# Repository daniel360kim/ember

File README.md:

# Ember

**A differentiable 6-DOF rocket simulator that trains a neural flight controller by backpropagating through physics.**

Ember is an end-to-end platform for developing thrust-vector-controlled (TVC) model rockets: a fully differentiable PyTorch flight dynamics engine, a neural attitude-control policy trained directly through the simulated physics, and a custom flight computer to fly the learned controller on real hardware.

The core idea is **differentiable simulation** (a.k.a. "diffsim"). Instead of treating the physics engine as an opaque, non-differentiable black box and learning a controller with reinforcement learning, Ember implements the entire 6-DOF rigid-body simulation in PyTorch so that gradients flow *through* every integration step, every aerodynamic force, and every actuator model. The attitude error at the end of a flight can be differentiated all the way back to the neural network's weights, letting the controller be optimized with plain gradient descent — the same way you would train any other neural network.

---

## Project status

Ember is an active work in progress. The current state:

**Working today**

- Complete, batched, GPU-ready 6-DOF differentiable physics (motor, TVC gimbal, aerodynamics, time-varying mass), integrated with RK4 and quaternion attitude kinematics.
- Batched rollout stack (`RocketEnv` + `EpisodeManager`) with flight-phase termination (burnout, ground impact, excessive tilt).
- A neural MLP attitude controller trained end-to-end through the physics via autograd, plus a PID baseline.
- Declarative YAML vehicle configuration.
- An extensive test suite (~40+ tests) including explicit gradient-flow verification.
- A custom Teensy-based flight computer designed in KiCad (`hardware/`).

**On the roadmap**

- Fully config-driven training/eval runners (task and hyperparameter YAML layers).
- Domain randomization over motor thrust, mass, servo lag, and drag for robust sim-to-real transfer.
- Trajectory-length masking of the loss past episode termination.
- Experiment logging, checkpointing, and a dedicated evaluation runner.
- Export of the trained policy to run in real time on the flight computer, closing the sim-to-hardware loop.

---

## Why differentiable simulation?

Learning a controller for an unstable, fast, safety-critical system like a TVC rocket is hard. The two conventional options each have a major drawback:

- **Reinforcement learning (RL)** treats the simulator as a black box and estimates gradients from scalar rewards. This works, but it is notoriously *sample-inefficient* — it throws away all the structure of the physics and needs enormous numbers of rollouts to converge.
- **Classical control (PID, LQR)** is sample-free but requires hand-tuning and a linearized model, and it struggles with the strongly time-varying, nonlinear dynamics of a rocket whose mass, center of gravity, and inertia change every millisecond as propellant burns.

Differentiable simulation gets the best of both. Because the physics engine is written in an autodiff framework, the *analytic gradient* of the flight outcome with respect to the controller parameters is available for free. Training becomes a direct optimization problem:

> "Given this rocket, what network weights minimize the attitude error over the boost phase?"

This is dramatically more sample-efficient than RL and far more flexible than classical control, because the exact gradient — not a noisy estimate — points the optimizer in the right direction on every single rollout.

```
                            ┌─────────────────────────────────────────────┐
   setpoint (upright) ─────►│  Neural Policy (MLP)                         │
                            │  attitude error + body rates → gimbal command│
                            └───────────────────┬─────────────────────────┘
                                                │  U (2-axis TVC torque cmd)
                                                ▼
        ┌───────────────────────────────────────────────────────────────┐
        │  Differentiable 6-DOF Physics (PyTorch)                        │
        │  motor thrust · TVC gimbal · aerodynamics · time-varying mass  │
        │  RK4 integration · quaternion attitude kinematics              │
        └───────────────────────────┬───────────────────────────────────┘
                                     │  trajectory X(t)   (fully differentiable)
                                     ▼
                            ┌────────────────────┐
                            │  Attitude-error    │
                            │  loss              │
                            └─────────┬──────────┘
                                      │
     ◄────────────────────────────────┘
        loss.backward(): gradient flows through the ENTIRE rollout,
        through every RK4 step and physics term, back to the MLP weights.
```

---

## How the differentiable simulation works

Everything in the physics path is a `torch.Tensor` operation, so the whole rollout is a single differentiable computation graph. A few deliberate engineering choices keep that graph intact and its gradients well-behaved:

- **Autograd through the integrator.** The RK4 step chains four evaluations of the vehicle dynamics per timestep, and every one is differentiable — the full trajectory is one continuous graph from initial condition to final state.

```21:27:simulation/src/vehicle/integrators.py
def rk4_step(...):
    k1 = dynamics_fn(X, U, t)
    k2 = dynamics_fn(X + dt / 2 * k1, U, t + dt / 2)
    k3 = dynamics_fn(X + dt / 2 * k2, U, t + dt / 2)
    k4 = dynamics_fn(X + dt * k3, U, t + dt)
    X_new = X + (dt / 6) * (k1 + 2 * k2 + 2 * k3 + k4)
```

- **Out-of-place quaternion normalization.** After each step the attitude quaternion is renormalized by constructing a *new* tensor rather than mutating in place, so backpropagation through the projection is safe (in-place writes are a classic way to silently break an autograd graph).

- **Branch-free physics.** Discontinuous logic — like the piecewise F15 thrust curve — is written with `torch.where` instead of Python `if` statements, so gradients propagate across every phase of the burn.

- **Gradient-safe numerics.** Operations that can produce infinite gradients (e.g. `arccos` at `±1` when computing angle of attack) clamp their inputs away from the singularity, keeping training stable.

Because the physics is written this way, `loss.backward()` on the training loss populates gradients on the neural network's parameters through thousands of chained physics operations, and a standard `Adam` optimizer step improves the controller. There is no reward function, no value network, and no policy-gradient estimator — just supervised optimization of a trajectory-level loss.

```53:69:simulation/src/runners/train_runner.py
        for i in range(N_EPOCHS):
            initial_state = torch.zeros(BATCH_DIM, S.DIM)
            initial_state[..., S.ORI] = start_orientation

            history = episode_runner.run(
                initial_state=initial_state,
                setpoint=setpoint,
                policy=policy,
                vehicle=self.vehicle,
            )

            loss = self.calculate_loss(history.to_episode_result(), setpoint=setpoint)

            print(f"Epoch {i + 1}/{N_EPOCHS} — loss: {loss.item():.6f}")
            optimizer.zero_grad()
            loss.backward()
            optimizer.step()
```

---

## The physics model

Ember simulates a full six-degree-of-freedom rigid body with a compact, batched 15-dimensional state vector (`simulation/src/vehicle/state.py`):

| State           | Indices | Description                                          |
| --------------- | :-----: | ---------------------------------------------------- |
| Position        | `0:3`   | World-frame position (Z up)                          |
| Orientation     | `3:7`   | Attitude quaternion, scalar-last `[x, y, z, w]`      |
| Velocity        | `7:10`  | World-frame linear velocity                          |
| Angular velocity| `10:13` | Body-frame angular rates                             |
| Gimbal angle    | `13:15` | 2-axis TVC deflections `(δx, δy)`                    |

Each timestep, the vehicle sums the physical forces and torques and integrates the rigid-body equations of motion. The physics is decomposed into independently-testable, composable components:

- **Motor** — a piecewise-polynomial F15 thrust curve with analytic total impulse and a time-varying propellant mass / moment-of-inertia model (inside-out burn).
- **Cartesian TVC gimbal** — a 2-axis thrust-vectoring actuator that tilts the thrust vector, with a first-order servo lag between commanded and actual deflection.
- **Aerodynamics** — quadratic drag, Barrowman-style normal force, and a pitch-damping moment.
- **Mass properties** — combines the dry airframe and burning motor, shifting the center of gravity and inertia tensor (via the parallel-axis theorem) as propellant is consumed.
- **Rigid-body core** — Newton–Euler dynamics including the gyroscopic term `ω × (Iω)`, integrated with swappable explicit-Euler or RK4 schemes.

The entire vehicle is specified declaratively in YAML (`simulation/configs/vehicles/atlas.yaml`) — mass, motor, geometry, aero coefficients, and gimbal limits — so a rocket is fully described by data rather than code.

---

## The neural controller

The policy is a small multilayer perceptron (`simulation/src/policy/mlp.py`) — deliberately kept tiny so it can eventually be exported and run in real time on a microcontroller. It observes the *shortest-path* body-frame attitude error (the x/y components of the error quaternion) together with the body angular rates, and outputs a 2-axis gimbal torque command squashed through `tanh` to respect the actuator's physical limits.

```26:38:simulation/src/policy/mlp.py
    def forward(self, X, setpoint):
        q  = normalize_quat(X[..., S.ORI])
        w_b = X[..., S.ANG_VEL]
        setpoint = normalize_quat(setpoint.expand(*q.shape[:-1], 4))

        q_error = quat_mul(quat_inv(q), setpoint)
        q_error = q_error * torch.where(q_error[..., 3:4] < 0, -1., 1.)
        error   = q_error[..., :2]

        input = torch.cat([error, X[..., S.ANG_VEL]], dim=-1)
        output = self.network(input)
        return self.max_output * torch.tanh(output)
```

A conventional **PID controller** (`simulation/src/policy/pid.py`) is included as a baseline for comparison against the learned policy.

---

## Quick start

Requires Python 3.10+.

```bash
git clone https://github.com/daniel360kim/ember.git
cd ember/simulation
pip install -e .
```

This installs `torch`, `numpy`, `matplotlib`, and `pyyaml`, and puts `src/` on the import path so `from vehicle.atlas_v1 import Atlas`-style imports resolve.

### Train the neural controller through the physics

```bash
cd ember/simulation
PYTHONPATH=src python src/runners/train_runner.py
```

This builds the `Atlas` vehicle, rolls it out under the MLP policy from a slightly tilted initial attitude, computes the attitude-error loss over the boost, and backpropagates through the entire flight to update the network — for 100 epochs. It plots the orientation and gimbal histories at the first, middle, and last epoch so you can watch the controller learn to stabilize the rocket.

### Run the test suite

The physics engine is covered by an extensive suite of unit and integration tests, including explicit checks that gradients flow correctly through the integrators, the rigid-body core, and the full vehicle dynamics.

```bash
cd ember/simulation
pytest                 # everything
pytest tests/vehicle/  # physics component & dynamics tests
pytest tests/runners/  # environment & rollout integration tests
```

---

## Repository layout

```
ember/
├── simulation/                     # Differentiable PyTorch simulator (main project)
│   ├── src/
│   │   ├── vehicle/                # 6-DOF physics
│   │   │   ├── atlas_v1.py         # Concrete rocket: assembles the full dynamics
│   │   │   ├── base_vehicle.py     # Vehicle interface + quaternion projection
│   │   │   ├── rigid_body.py       # Newton–Euler derivative core
│   │   │   ├── mass_properties.py  # Time-varying mass / CG / inertia
│   │   │   ├── integrators.py      # euler_step, rk4_step (differentiable)
│   │   │   ├── state.py            # 15-D state-vector layout
│   │   │   └── components/         # motor, cartesian_gimbal (TVC), aero
│   │   ├── policy/
│   │   │   ├── mlp.py              # Neural attitude controller
│   │   │   └── pid.py              # Classical baseline
│   │   ├── runners/
│   │   │   ├── rocket_env.py       # Batched, Gym-like physics environment
│   │   │   ├── episode_manager.py  # Policy-in-the-loop rollout engine
│   │   │   └── train_runner.py     # Differentiable training entry point
│   │   └── utils/math.py           # Quaternion algebra & kinematics
│   ├── configs/vehicles/atlas.yaml # Declarative vehicle definition
│   └── tests/                      # Physics unit tests + gradient-flow checks
│
├── hardware/                       # Custom flight computer (KiCad)
│   └── pcb/flight_computer/        # Teensy-based board: IMU, barometer,
│                                   # servo drivers, pyro channels, power
└── background/                     # Early diffsim prototypes & experiments
```

---

## Hardware

The `hardware/` directory contains the KiCad design for a custom rocket flight computer — a Teensy-class board with an IMU, barometer, servo drivers for the TVC gimbal, pyro channels for recovery, and power management. The long-term goal of Ember is **zero-shot sim-to-real transfer**: train the attitude controller entirely in the differentiable simulator, then deploy the exact learned weights to this board to fly a physical rocket.

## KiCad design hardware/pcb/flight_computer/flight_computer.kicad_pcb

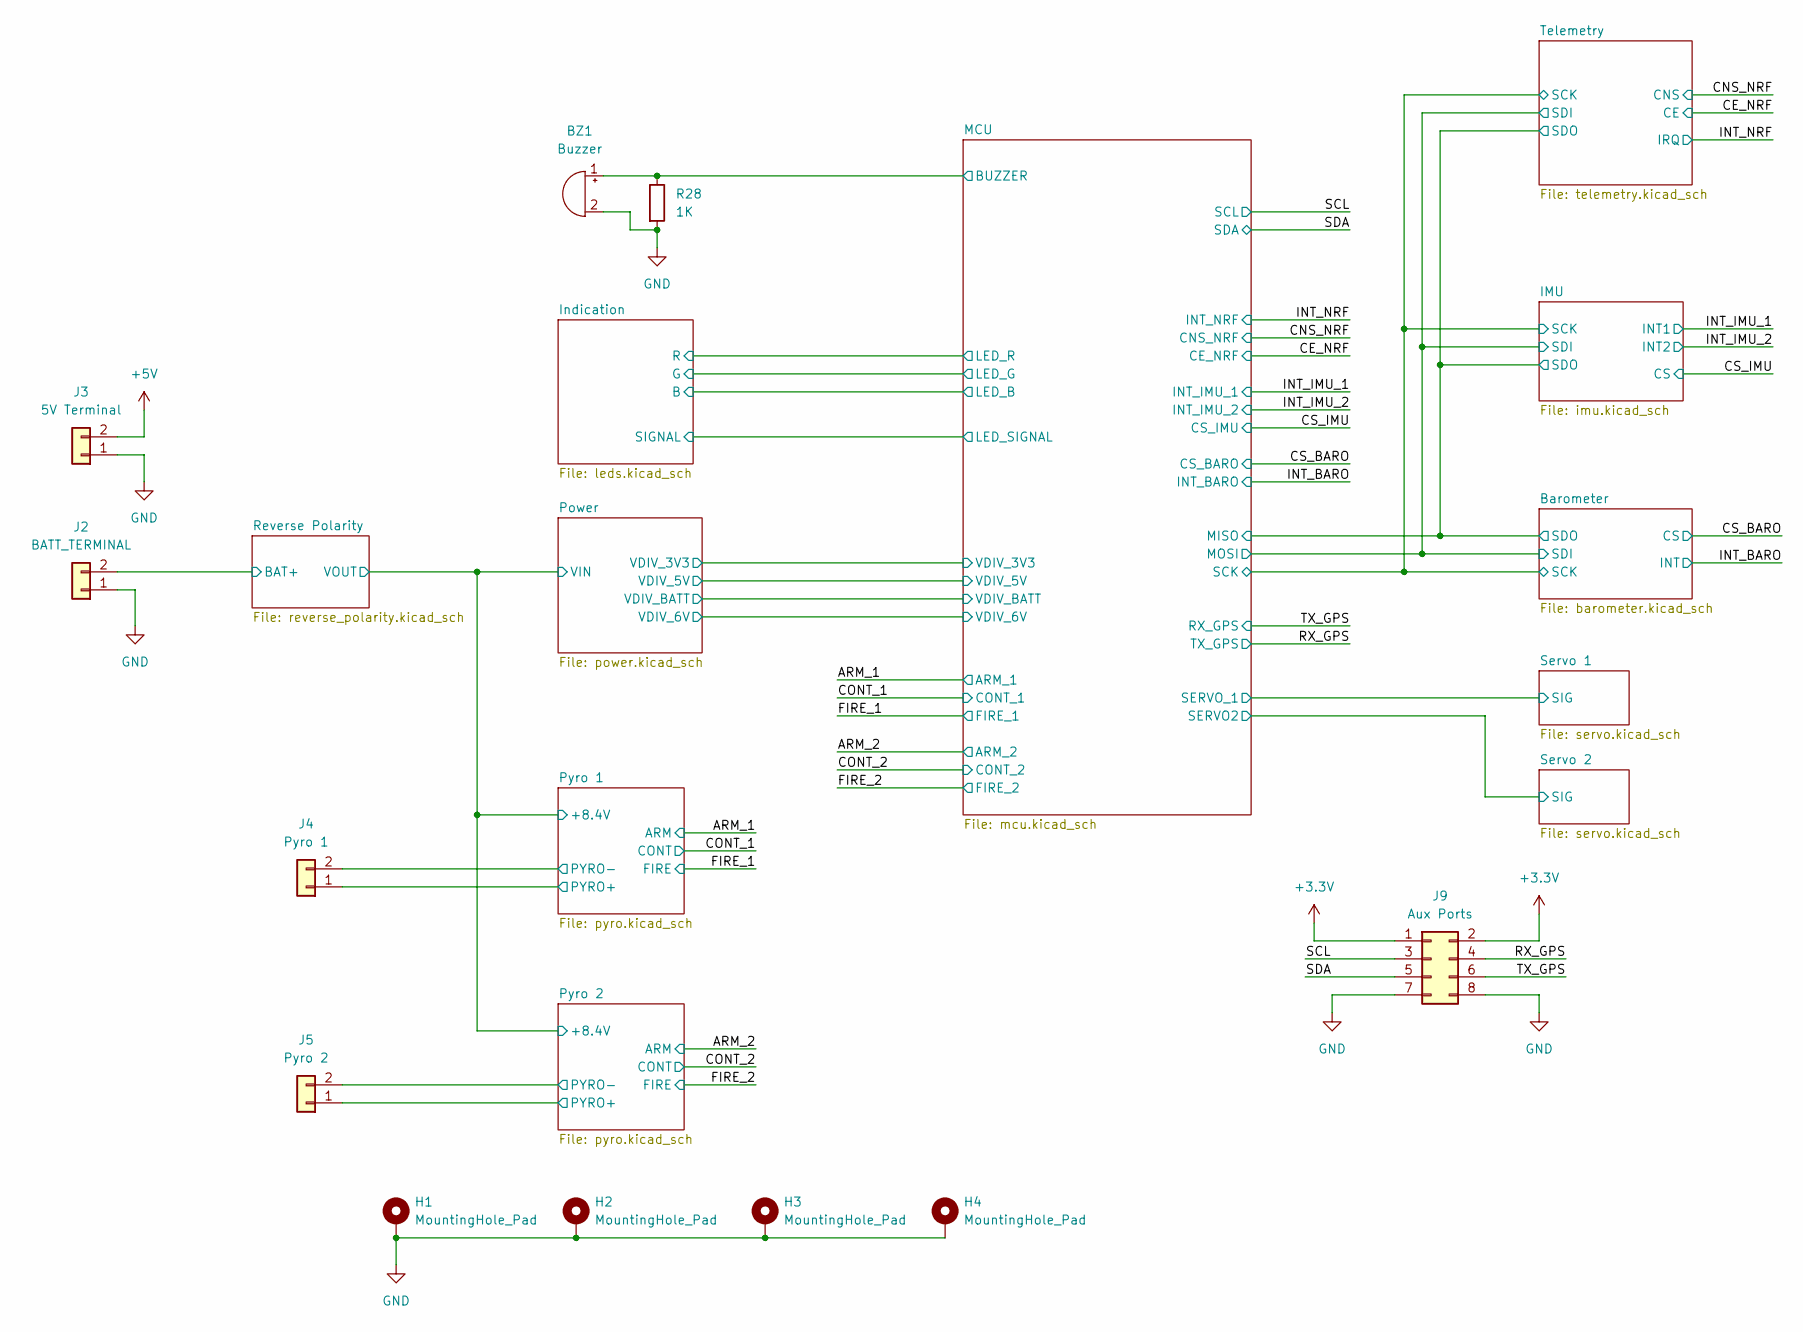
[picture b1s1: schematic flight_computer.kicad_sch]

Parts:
BZ1: Buzzer; Buzzer_Murata_PKMCS0909E
H1, H2, H3, H4: MountingHole_Pad; MountingHole_3mm_Pad
J2: BATT_TERMINAL; 691502710002
J3: 5V Terminal; 691502710002
J4: Pyro 1; 691502710002
J5: Pyro 2; 691502710002
J9: Aux Ports; PinHeader_2x04_P2.54mm_Vertical
R28: 1K; R_0603_1608Metric

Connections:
+3.3V: J9.1, J9.2; also elsewhere on the board
+5V: J3.2; also elsewhere on the board
/MCU/BUZZER: BZ1.1 (-), R28.1; also elsewhere on the board
/Pyro 1/PYRO+: J4.1; also elsewhere on the board
/Pyro 1/PYRO-: J4.2; also elsewhere on the board
/Pyro 2/PYRO+: J5.1; also elsewhere on the board
/Pyro 2/PYRO-: J5.2; also elsewhere on the board
/RX_GPS: J9.4; also elsewhere on the board
/Reverse Polarity/BAT+: J2.2; also elsewhere on the board
/SCL: J9.3; also elsewhere on the board
/SDA: J9.5; also elsewhere on the board
/TX_GPS: J9.6; also elsewhere on the board
GND: BZ1.2 (+), H1.1 (1_1), H2.1 (1_1), H3.1 (1_1), H4.1 (1_1), J2.1, J3.1, J9.7, J9.8, R28.2; also elsewhere on the board

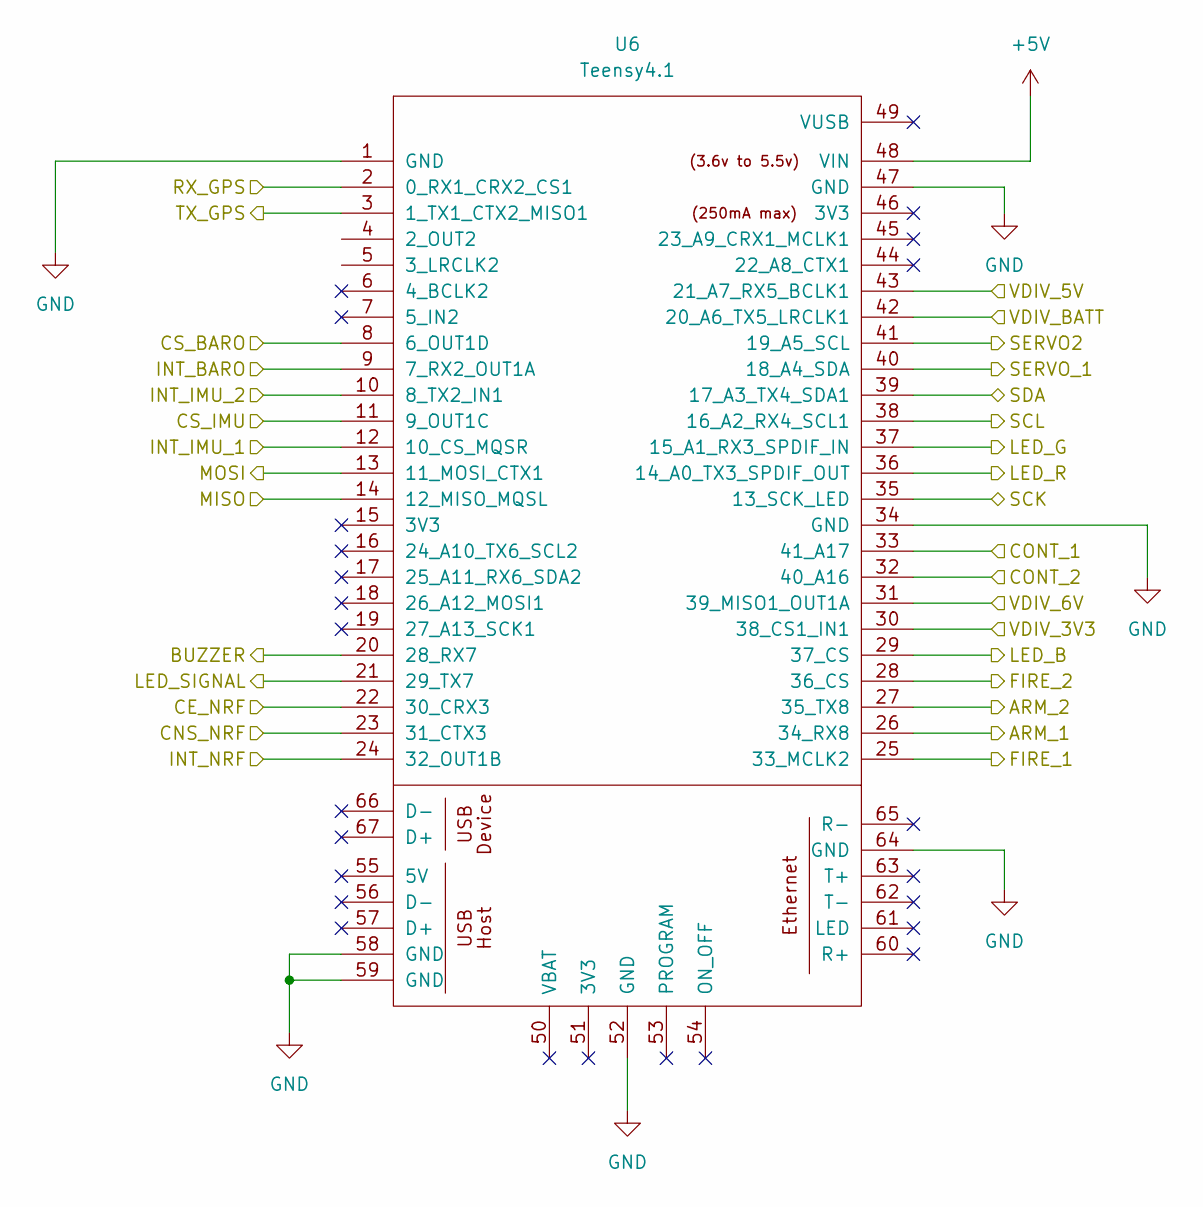
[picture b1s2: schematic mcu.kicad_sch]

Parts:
U6: Teensy4.1; Teensy41

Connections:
+5V: U6.48 (VIN); also elsewhere on the board
/ARM_1: U6.26 (34_RX8); also elsewhere on the board
/ARM_2: U6.27 (35_TX8); also elsewhere on the board
/Barometer/SCK: U6.35 (13_SCK_LED); also elsewhere on the board
/Barometer/SDI: U6.13 (11_MOSI_CTX1); also elsewhere on the board
/Barometer/SDO: U6.14 (12_MISO_MQSL); also elsewhere on the board
/CE_NRF: U6.22 (30_CRX3); also elsewhere on the board
/CNS_NRF: U6.23 (31_CTX3); also elsewhere on the board
/CONT_1: U6.33 (41_A17); also elsewhere on the board
/CONT_2: U6.32 (40_A16); also elsewhere on the board
/CS_BARO: U6.8 (6_OUT1D); also elsewhere on the board
/CS_IMU: U6.11 (9_OUT1C); also elsewhere on the board
/FIRE_1: U6.25 (33_MCLK2); also elsewhere on the board
/FIRE_2: U6.28 (36_CS); also elsewhere on the board
/INT_BARO: U6.9 (7_RX2_OUT1A); also elsewhere on the board
/INT_IMU_1: U6.12 (10_CS_MQSR); also elsewhere on the board
/INT_IMU_2: U6.10 (8_TX2_IN1); also elsewhere on the board
/INT_NRF: U6.24 (32_OUT1B); also elsewhere on the board
/Indication/B: U6.29 (37_CS); also elsewhere on the board
/Indication/G: U6.37 (15_A1_RX3_SPDIF_IN); also elsewhere on the board
/Indication/R: U6.36 (14_A0_TX3_SPDIF_OUT); also elsewhere on the board
/Indication/SIGNAL: U6.21 (29_TX7); also elsewhere on the board
/MCU/BUZZER: U6.20 (28_RX7); also elsewhere on the board
/MCU/SERVO2: U6.41 (19_A5_SCL); also elsewhere on the board
/MCU/SERVO_1: U6.40 (18_A4_SDA); also elsewhere on the board
/MCU/VDIV_3V3: U6.30 (38_CS1_IN1); also elsewhere on the board
/MCU/VDIV_5V: U6.43 (21_A7_RX5_BCLK1); also elsewhere on the board
/MCU/VDIV_6V: U6.31 (39_MISO1_OUT1A); also elsewhere on the board
/MCU/VDIV_BATT: U6.42 (20_A6_TX5_LRCLK1); also elsewhere on the board
/RX_GPS: U6.3 (1_TX1_CTX2_MISO1); also elsewhere on the board
/SCL: U6.38 (16_A2_RX4_SCL1); also elsewhere on the board
/SDA: U6.39 (17_A3_TX4_SDA1); also elsewhere on the board
/TX_GPS: U6.2 (0_RX1_CRX2_CS1); also elsewhere on the board
GND: U6.1 (GND), U6.34 (GND), U6.47 (GND), U6.52 (GND), U6.58 (GND), U6.59 (GND), U6.64 (GND); also elsewhere on the board

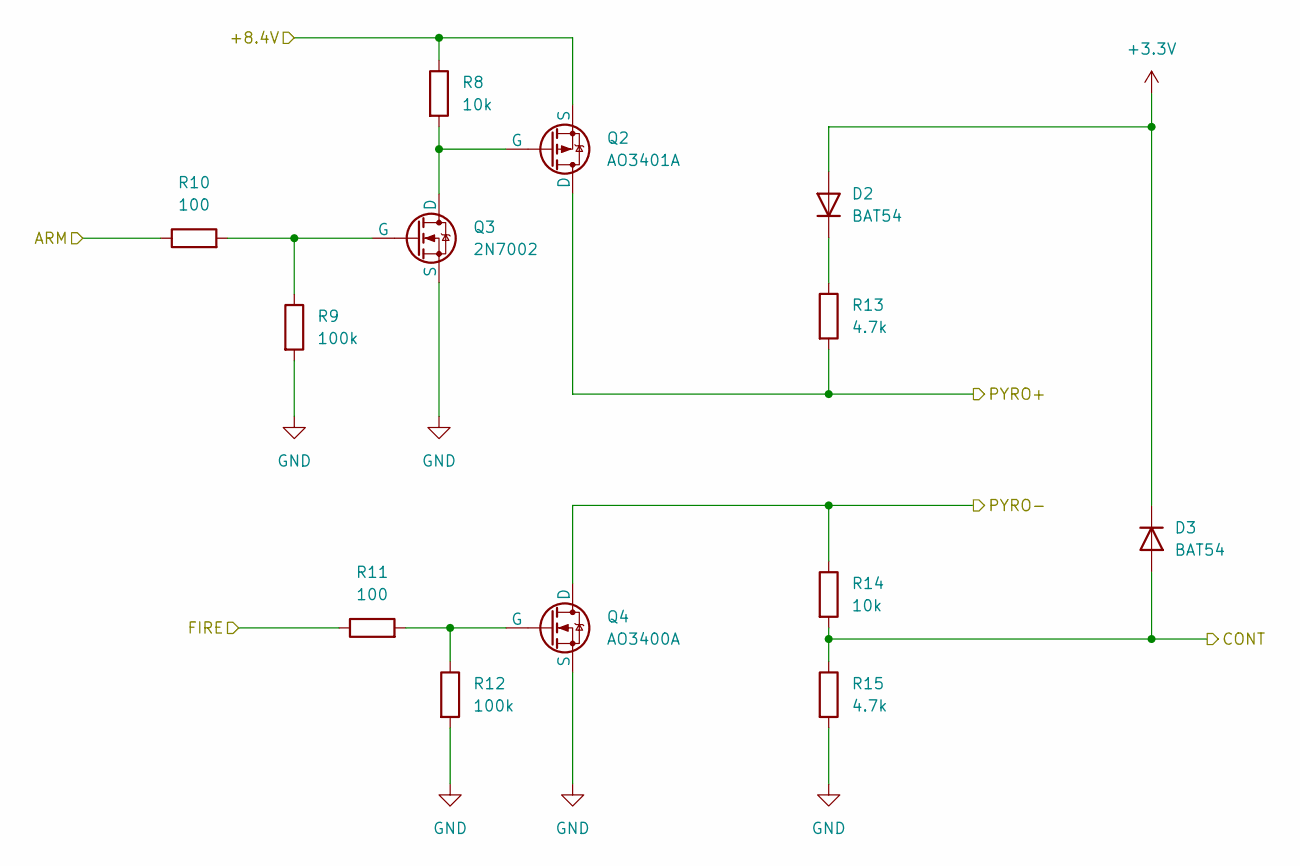
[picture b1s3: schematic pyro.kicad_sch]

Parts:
D2, D3: BAT54; SOT95P240X120-3N
Q2: AO3401A; SOT95P240X120-3N
Q3: 2N7002; SOT95P240X111-3N
Q4: AO3400A; SOT95P240X120-3N
R8, R14: 10k; R_0603_1608Metric
R9, R12: 100k; R_0603_1608Metric
R10, R11: 100; R_0603_1608Metric
R13, R15: 4.7k; R_0603_1608Metric

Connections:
+3.3V: D2.2 (A), D3.1 (K); also elsewhere on the board
/ARM_1: R10.1; also elsewhere on the board
/CONT_1: D3.2 (A), R14.2, R15.1; also elsewhere on the board
/FIRE_1: R11.1; also elsewhere on the board
/Power/VIN: Q2.3 (S), R8.1; also elsewhere on the board
/Pyro 1/PYRO+: Q2.1 (D), R13.2; also elsewhere on the board
/Pyro 1/PYRO-: Q4.1 (D), R14.1; also elsewhere on the board
GND: Q3.3 (S), Q4.3 (S), R9.2, R12.2, R15.2; also elsewhere on the board
unnamed: D2.1 (K), R13.1
unnamed: Q2.2 (G), Q3.1 (D), R8.2
unnamed: Q3.2 (G), R9.1, R10.2
unnamed: Q4.2 (G), R11.2, R12.1

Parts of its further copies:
D4, D5: BAT54; SOT95P240X120-3N
Q5: 2N7002; SOT95P240X111-3N
Q6: AO3401A; SOT95P240X120-3N
Q7: AO3400A; SOT95P240X120-3N
R20, R22: 100; R_0603_1608Metric
R21, R24: 100k; R_0603_1608Metric
R23, R26: 10k; R_0603_1608Metric
R25, R27: 4.7k; R_0603_1608Metric

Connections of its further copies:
+3.3V: D4.2 (A), D5.1 (K); also elsewhere on the board
/ARM_2: R20.1; also elsewhere on the board
/CONT_2: D5.2 (A), R26.2, R27.1; also elsewhere on the board
/FIRE_2: R22.1; also elsewhere on the board
/Power/VIN: Q6.3 (S), R23.1; also elsewhere on the board
/Pyro 2/PYRO+: Q6.1 (D), R25.2; also elsewhere on the board
/Pyro 2/PYRO-: Q7.1 (D), R26.1; also elsewhere on the board
GND: Q5.3 (S), Q7.3 (S), R21.2, R24.2, R27.2; also elsewhere on the board
unnamed: D4.1 (K), R25.1
unnamed: Q5.1 (D), Q6.2 (G), R23.2
unnamed: Q5.2 (G), R20.2, R21.1
unnamed: Q7.2 (G), R22.2, R24.1

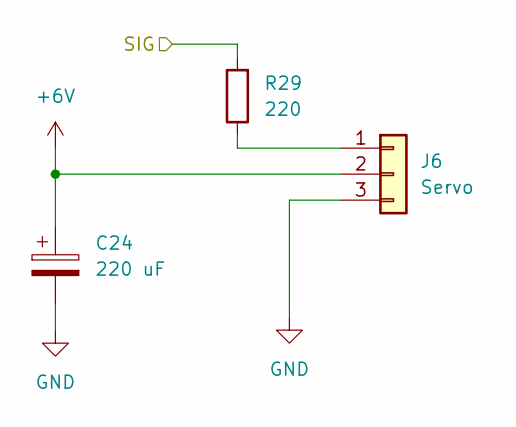
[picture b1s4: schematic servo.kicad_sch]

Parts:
C24: 220 uF; CAP_UCD_6P3X7P7_NCH
J6: Servo; PinHeader_1x03_P2.54mm_Vertical
R29: 220; R_0603_1608Metric

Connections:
+6V: C24.1, J6.2; also elsewhere on the board
/MCU/SERVO_1: R29.2; also elsewhere on the board
GND: C24.2, J6.3; also elsewhere on the board
unnamed: J6.1, R29.1

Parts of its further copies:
C25: 220 uF; CAP_UCD_6P3X7P7_NCH
J7: Servo; PinHeader_1x03_P2.54mm_Vertical
R36: 220; R_0603_1608Metric

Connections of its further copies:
+6V: C25.1, J7.2; also elsewhere on the board
/MCU/SERVO2: R36.2; also elsewhere on the board
GND: C25.2, J7.3; also elsewhere on the board
unnamed: J7.1, R36.1

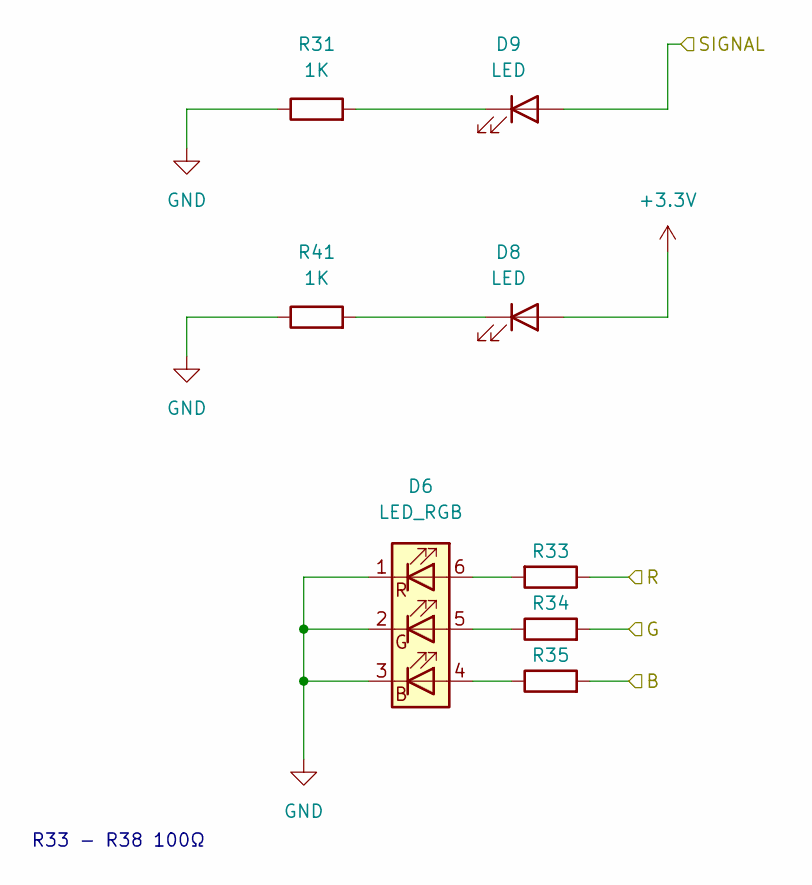
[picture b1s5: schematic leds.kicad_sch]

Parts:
D6: LED_RGB; LED_RGB_5050-6
D8, D9: LED; LED_0603_1608Metric
R31, R41: 1K; R_0603_1608Metric
R33, R35: R; R_0603_1608Metric
R34: R_0603_1608Metric

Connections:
+3.3V: D8.2 (A); also elsewhere on the board
/Indication/B: R35.2; also elsewhere on the board
/Indication/G: R34.2; also elsewhere on the board
/Indication/R: R33.1; also elsewhere on the board
/Indication/SIGNAL: D9.2 (A); also elsewhere on the board
GND: D6.1 (RK), D6.2 (GK), D6.3 (BK), R31.1, R41.1; also elsewhere on the board
unnamed: D6.4 (BA), R35.1
unnamed: D6.5 (GA), R34.1
unnamed: D6.6 (RA), R33.2
unnamed: D8.1 (K), R41.2
unnamed: D9.1 (K), R31.2

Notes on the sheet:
R33 - R38 100Ω

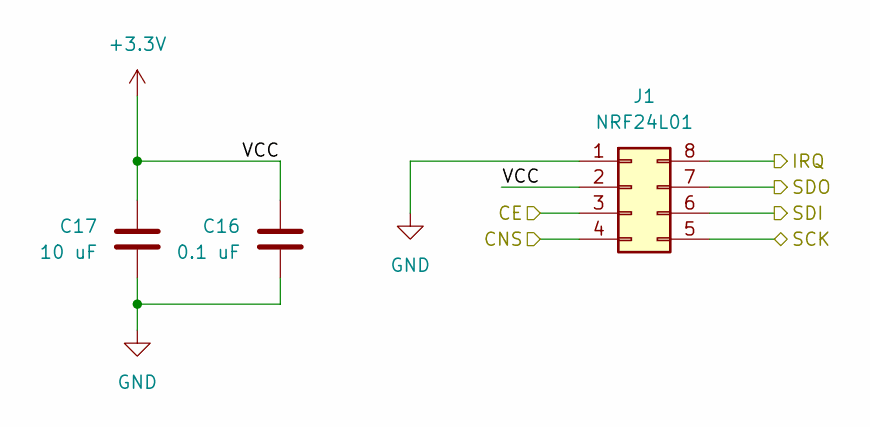
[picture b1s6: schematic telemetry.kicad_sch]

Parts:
C16: 0.1 uF; C_0603_1608Metric
C17: 10 uF; C_0603_1608Metric
J1: NRF24L01; PinHeader_2x04_P2.54mm_Vertical

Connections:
+3.3V: C16.1, C17.1, J1.2; also elsewhere on the board
/Barometer/SCK: J1.5; also elsewhere on the board
/Barometer/SDI: J1.6; also elsewhere on the board
/Barometer/SDO: J1.7; also elsewhere on the board
/CE_NRF: J1.3; also elsewhere on the board
/CNS_NRF: J1.4; also elsewhere on the board
/INT_NRF: J1.8; also elsewhere on the board
GND: C16.2, C17.2, J1.1; also elsewhere on the board

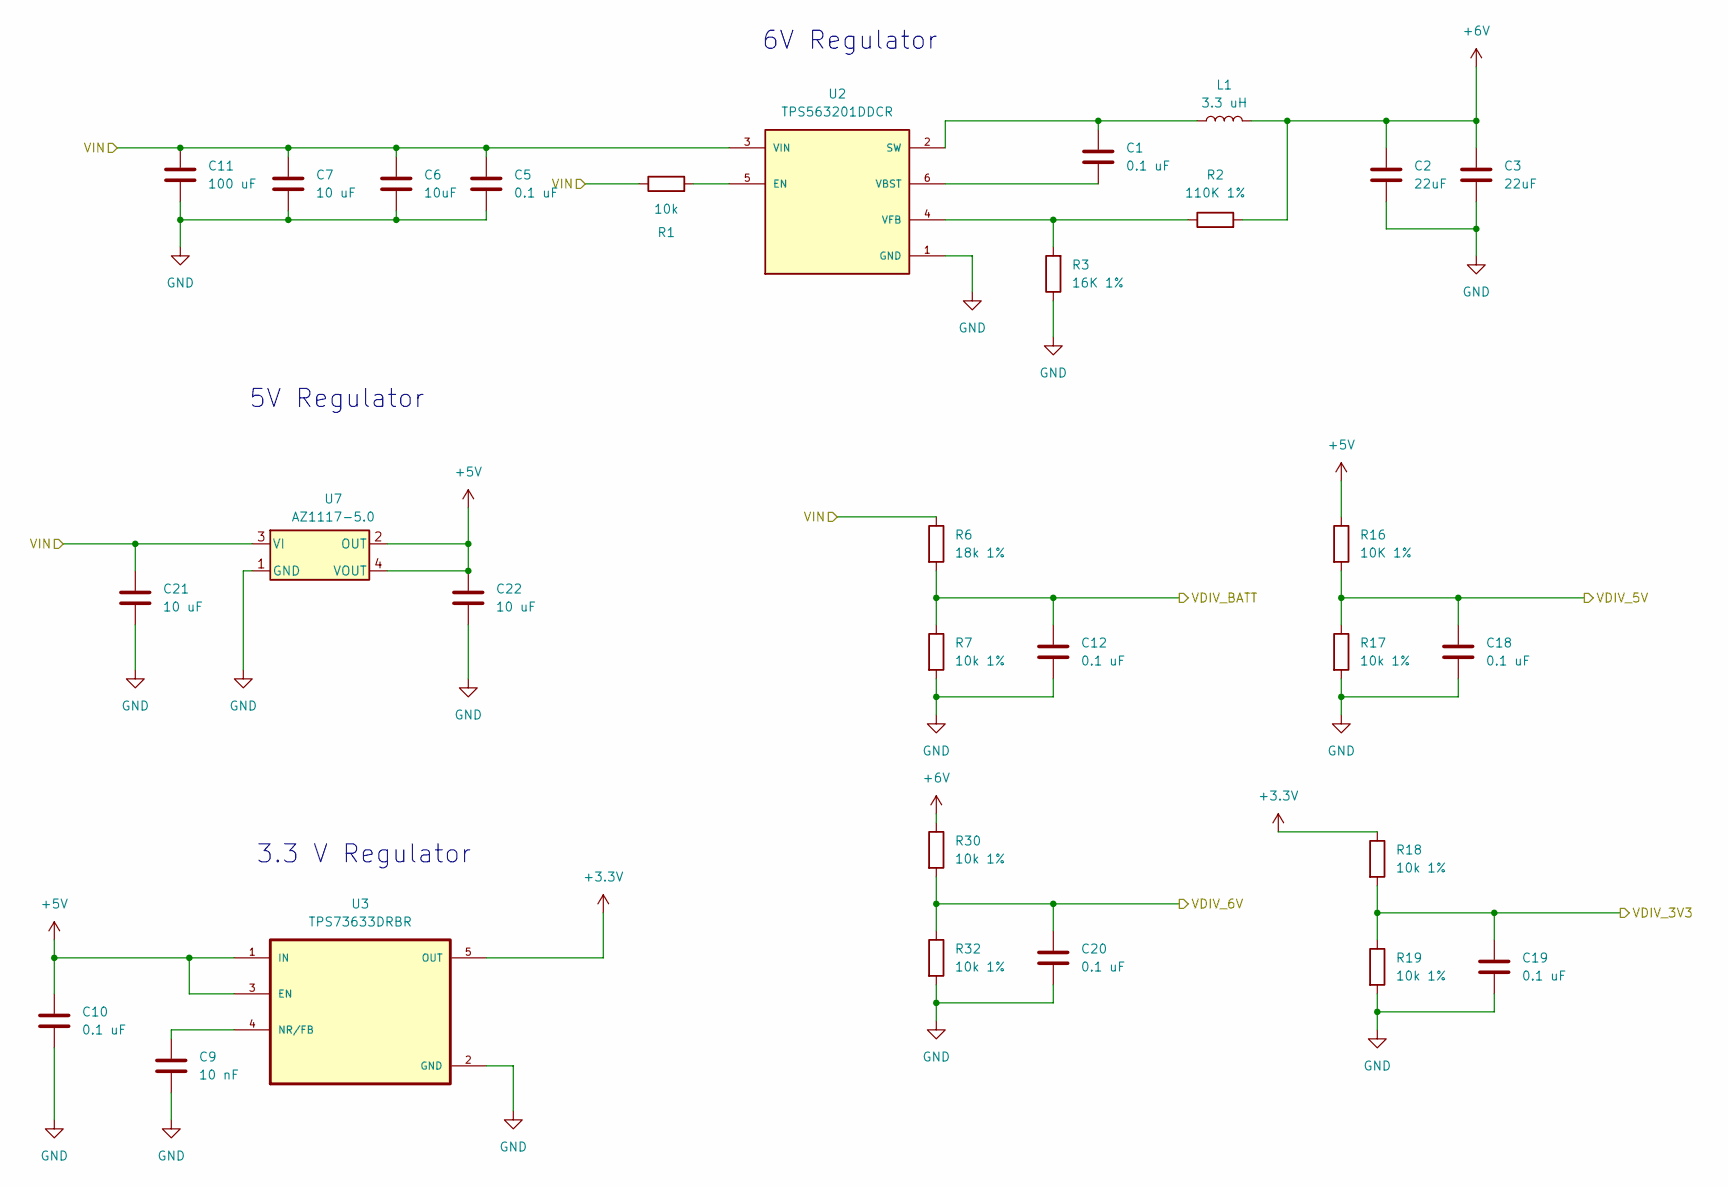
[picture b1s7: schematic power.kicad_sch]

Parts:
C1, C5, C10, C12, C18, C19, C20: 0.1 uF; C_0603_1608Metric
C2, C3: 22uF; C_0603_1608Metric
C6: 10uF; C_0603_1608Metric
C7, C21, C22: 10 uF; C_0603_1608Metric
C9: 10 nF; C_0603_1608Metric
C11: 100 uF; WCAP-ASLI_6.3X7.7_DXL_
L1: 3.3 uH; L_0603_1608Metric
R1: 10k; R_0603_1608Metric
R2: 110K 1%; R_0603_1608Metric
R3: 16K 1%; R_0603_1608Metric
R6: 18k 1%; R_0603_1608Metric
R7, R17, R18, R19, R30, R32: 10k 1%; R_0603_1608Metric
R16: 10K 1%; R_0603_1608Metric
U2: TPS563201DDCR; SOT95P280X110-6N; PARTREV December 2015
U3: TPS73633DRBR; SOT95P280X145-5N
U7: AZ1117-5.0; SOT223-5_DIO

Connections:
+3.3V: R18.1, U3.5 (OUT); also elsewhere on the board
+5V: C10.1, C22.1, R16.1, U3.1 (IN), U3.3 (EN), U7.2 (OUT), U7.4 (VOUT); also elsewhere on the board
+6V: C2.1, C3.1, L1.2, R2.2, R30.1; also elsewhere on the board
/MCU/VDIV_3V3: C19.1, R18.2, R19.1; also elsewhere on the board
/MCU/VDIV_5V: C18.1, R16.2, R17.1; also elsewhere on the board
/MCU/VDIV_6V: C20.1, R30.2, R32.1; also elsewhere on the board
/MCU/VDIV_BATT: C12.1, R6.2, R7.1; also elsewhere on the board
/Power/VIN: C5.1, C6.1, C7.1, C11.1, C21.1, R1.1, R6.1, U2.3 (VIN), U7.3 (VI); also elsewhere on the board
GND: C2.2, C3.2, C5.2, C6.2, C7.2, C9.2, C10.2, C11.2, C12.2, C18.2, C19.2, C20.2, C21.2, C22.2, R3.1, R7.2, R17.2, R19.2, R32.2, U2.1 (GND), U3.2 (GND), U7.1 (GND); also elsewhere on the board
unnamed: R1.2, U2.5 (EN)
unnamed: C1.1, L1.1, U2.2 (SW)
unnamed: C1.2, U2.6 (VBST)
unnamed: R2.1, R3.2, U2.4 (VFB)
unnamed: C9.1, U3.4 (NR/FB)

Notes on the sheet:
6V Regulator
5V Regulator
3.3 V Regulator

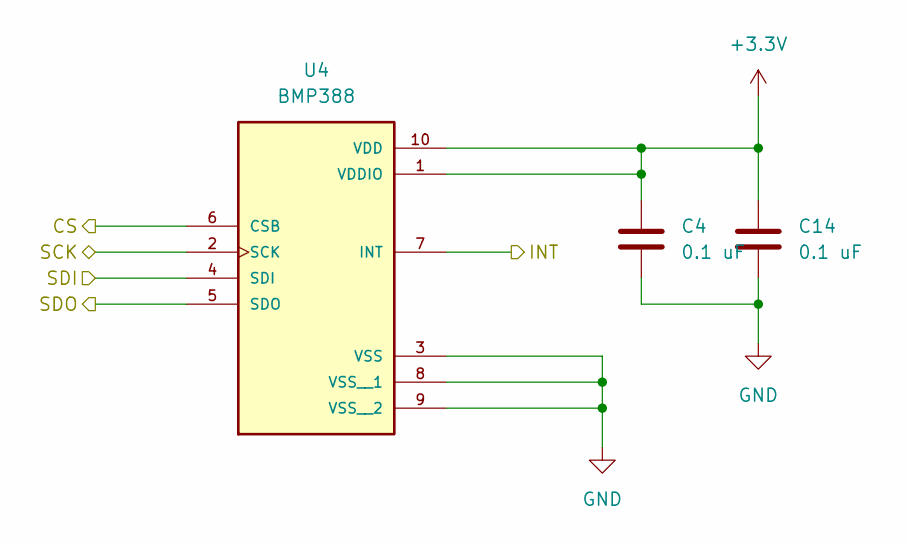
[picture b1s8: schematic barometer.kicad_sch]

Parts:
C4, C14: 0.1 uF; C_0603_1608Metric
U4: BMP388; XDCR_BMP388; PARTREV 1.7

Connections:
+3.3V: C4.1, C14.1, U4.1 (VDDIO), U4.10 (VDD); also elsewhere on the board
/Barometer/SCK: U4.2 (SCK); also elsewhere on the board
/Barometer/SDI: U4.4 (SDI); also elsewhere on the board
/Barometer/SDO: U4.5 (SDO); also elsewhere on the board
/CS_BARO: U4.6 (CSB); also elsewhere on the board
/INT_BARO: U4.7 (INT); also elsewhere on the board
GND: C4.2, C14.2, U4.3 (VSS), U4.8 (VSS__1), U4.9 (VSS__2); also elsewhere on the board

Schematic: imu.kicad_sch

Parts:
C13, C15: 0.1 uF; C_0603_1608Metric
U5: LSM6DSRXTR; LGA-14L_STM

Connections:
+3.3V: C13.1, C15.1, U5.5 (VDDIO), U5.8 (VDD); also elsewhere on the board
/Barometer/SCK: U5.13 (SCL); also elsewhere on the board
/Barometer/SDI: U5.14 (SDA); also elsewhere on the board
/Barometer/SDO: U5.1 (SDO/SA0); also elsewhere on the board
/CS_IMU: U5.12 (CS); also elsewhere on the board
/INT_IMU_1: U5.4 (INT1); also elsewhere on the board
/INT_IMU_2: U5.9 (INT2); also elsewhere on the board
GND: C13.2, C15.2, U5.2 (SDX), U5.3 (SCX), U5.6 (GND), U5.7 (GND); also elsewhere on the board

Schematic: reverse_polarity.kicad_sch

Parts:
D7: BZT52C5V1; P35_SOD-123F; PARTREV 31 Aug 2016
Q1: AO3401A; SOT95P240X120-3N
R37: 100k; R_0603_1608Metric
R38: 10k; R_0603_1608Metric

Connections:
/Power/VIN: D7.1, Q1.3 (S); also elsewhere on the board
/Reverse Polarity/BAT+: Q1.1 (D); also elsewhere on the board
GND: R37.2; also elsewhere on the board
unnamed: D7.2, R37.1, R38.2
unnamed: Q1.2 (G), R38.1

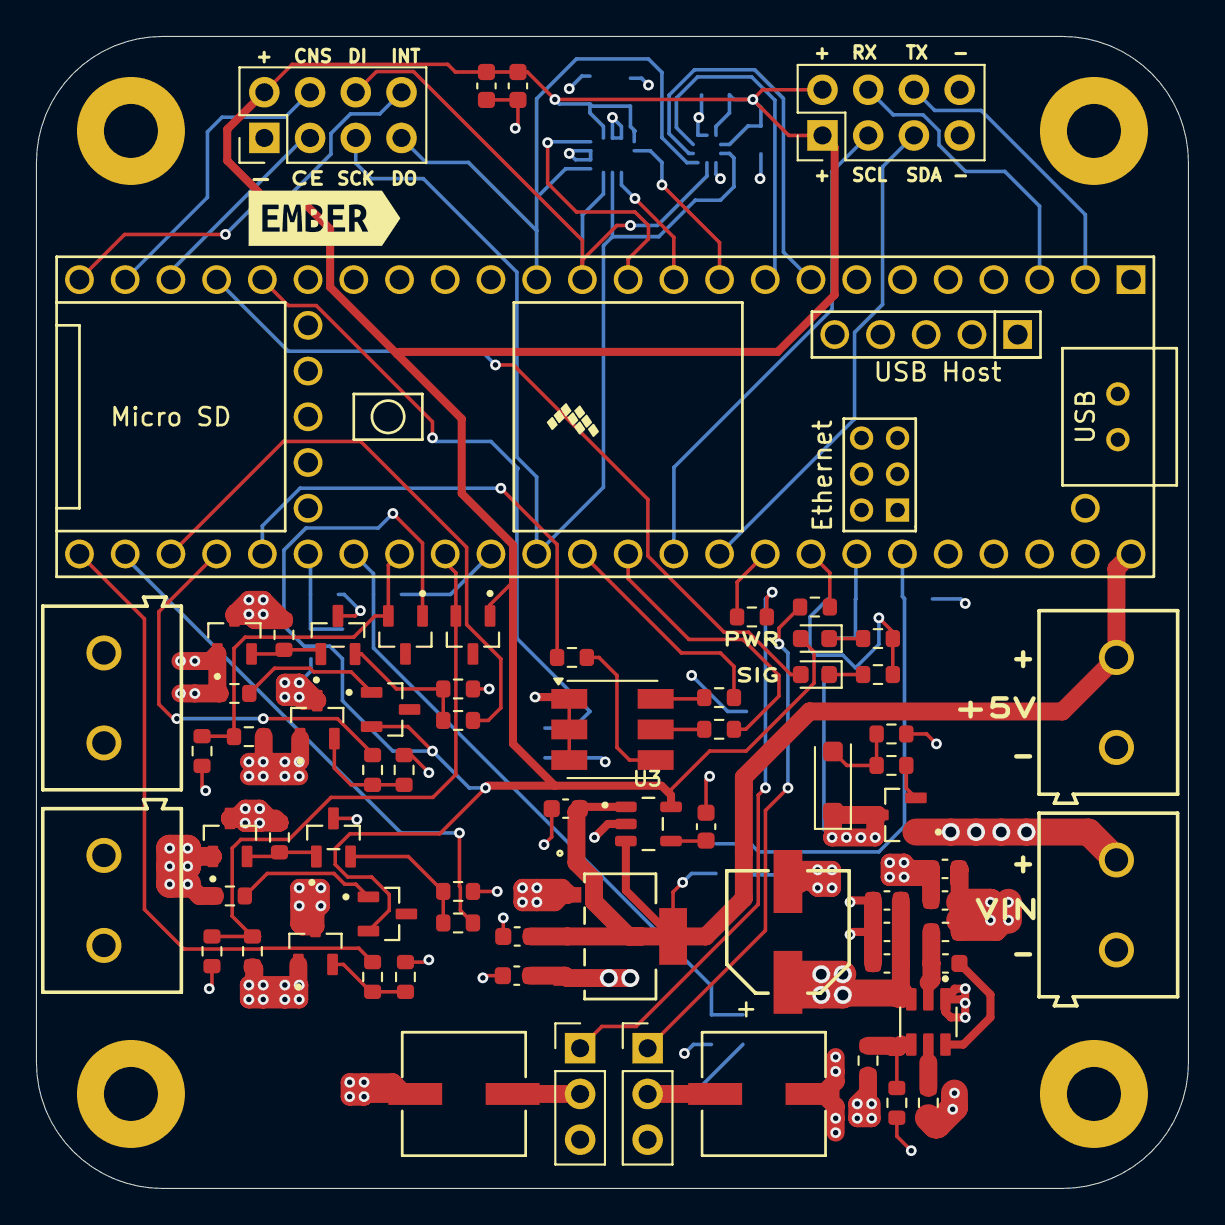
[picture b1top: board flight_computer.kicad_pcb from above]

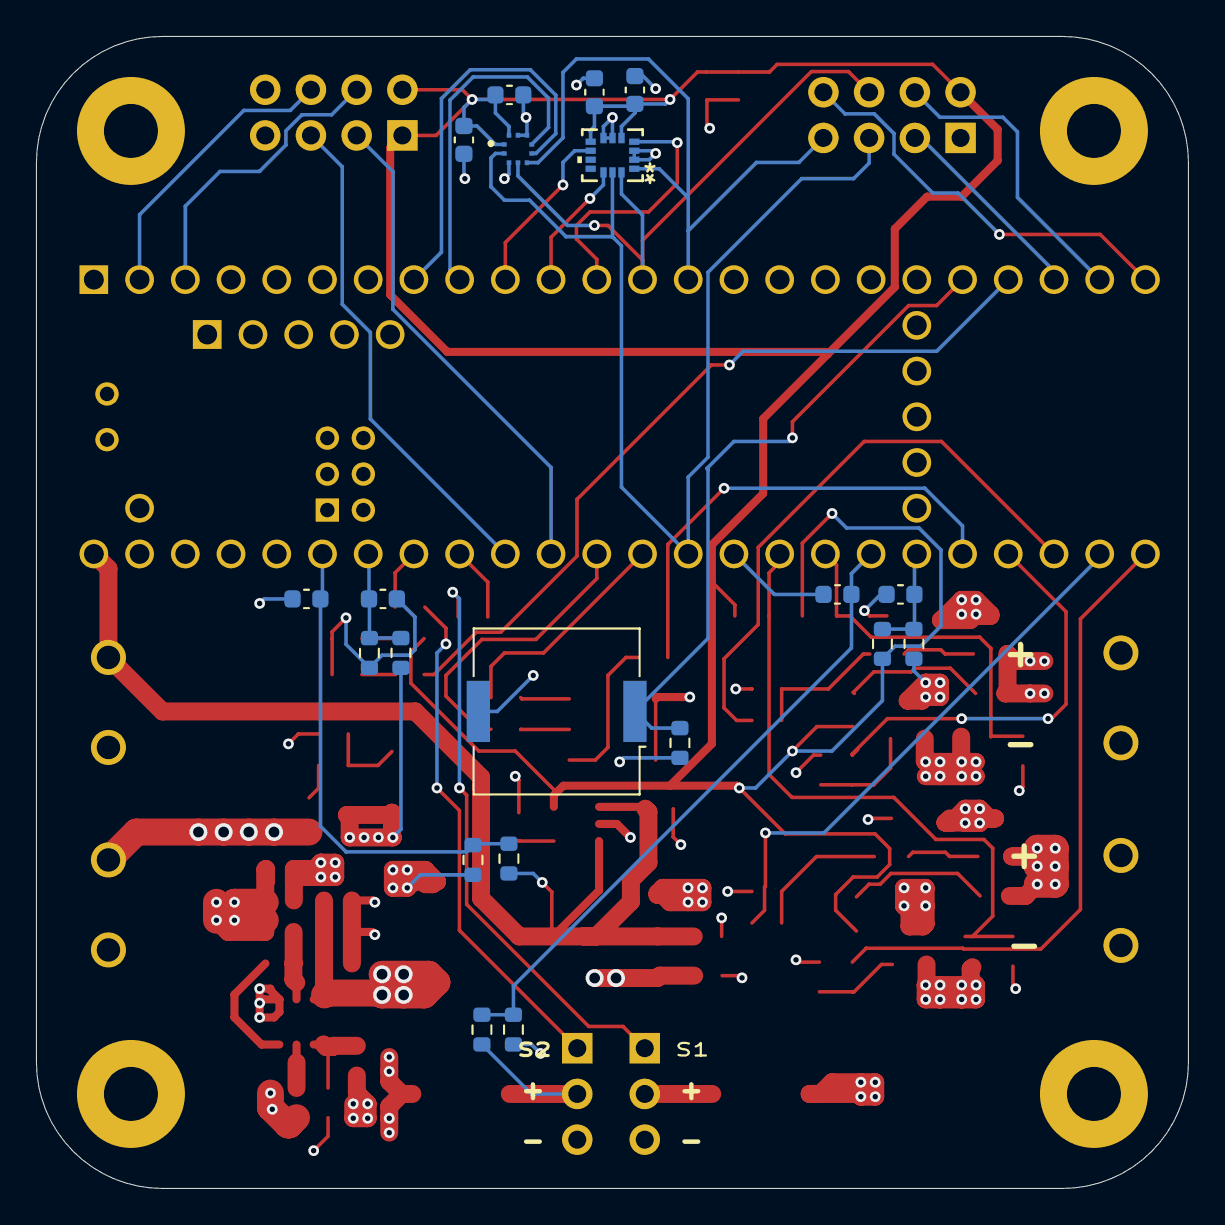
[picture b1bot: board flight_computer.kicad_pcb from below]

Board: 4 copper layers, 64.0 x 64.0 mm, 96 parts (20 on the bottom side), 64 nets.

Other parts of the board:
kibuzzard-6A2E09AC: G***; kibuzzard-6A2E09AC

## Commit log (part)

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2026-06-09 Added 3D model
2026-06-20 completed F15 motor class
2026-06-20 Created initial 1D simulation
2026-06-21 Included mass motor
2026-06-21 Added state class abstraction
2026-06-21 Implemented config files
2026-06-21 Implemented batching
2026-06-22 Implemented drag force torques
2026-06-22 updated plotting of rotational dynamics
2026-06-23 fab ready pcb
2026-06-24 implemented damping torque
2026-06-25 Added motor parameters to config file
2026-06-27 Implemented thrust vector control mount
2026-06-27 Implemented PID policy
2026-06-27 Replaced placeholder with actual control output
2026-06-27 Modeled shifting CG
2026-06-28 Modeled shifting MMOI
2026-06-28 added tests
